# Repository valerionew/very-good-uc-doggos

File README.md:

# very-good-uc-doggos
A special graduation present for a special friend. Six microcontrollers in one devboard

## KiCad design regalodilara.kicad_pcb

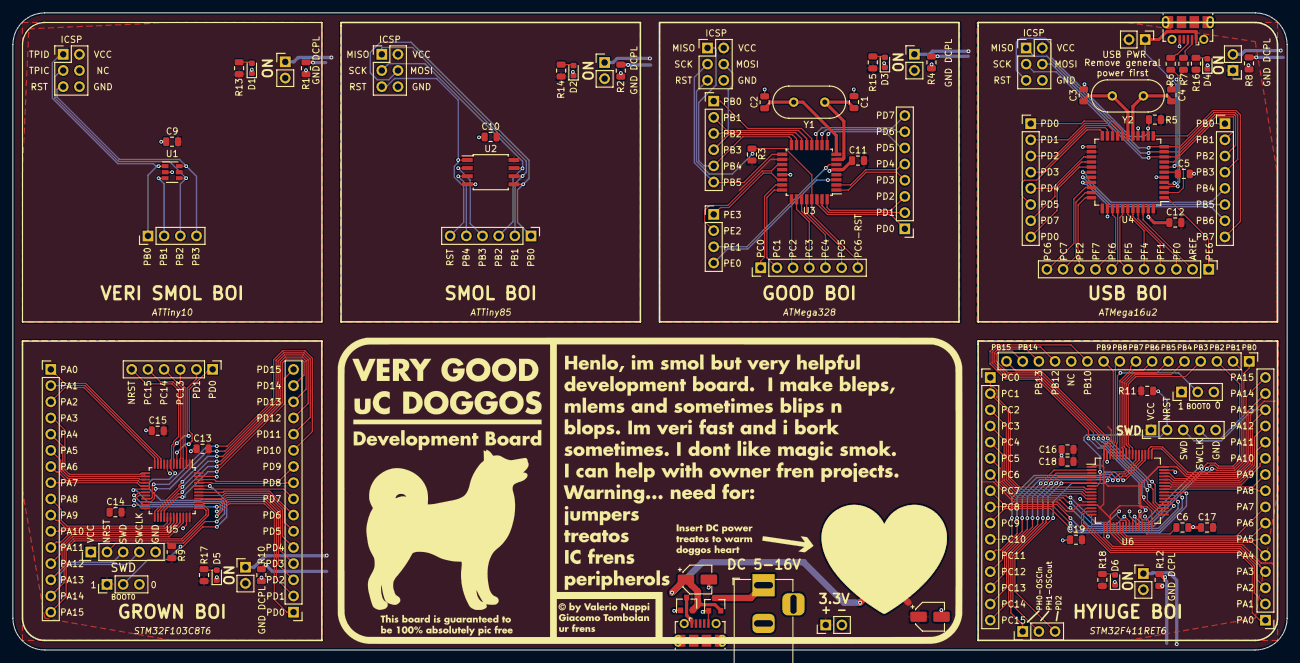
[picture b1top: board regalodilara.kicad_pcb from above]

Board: 2 copper layers, 200.0 x 100.0 mm, 89 parts (0 on the bottom side), 188 nets.

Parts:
C1, C2, C3, C4: C_Small; C_0805_2012Metric
C5: 1u; C_0805_2012Metric
C6: 2.2u; C_0805_2012Metric
C7, C8: 10u; CP_Elec_4x5.4
C9, C10, C11, C12, C13, C14, C15, C16, C17, C18, C19: 100n; C_0805_2012Metric
D1, D2, D3, D4, D5, D6: LED; LED_0603_1608Metric
J1, J4, J9, J13: ICSP; PinHeader_2x03_P2.54mm_Vertical
J2, J5, J7, J18, J24, J33: Conn_01x02; PinHeader_1x02_P2.54mm_Vertical
J3, J11: Conn_01x04; PinHeader_1x04_P2.54mm_Vertical
J6, J8: Conn_01x06; PinHeader_1x06_P2.54mm_Vertical
J10: Conn_01x07; PinHeader_1x07_P2.54mm_Vertical
J12, J14, J15: Conn_01x08; PinHeader_1x08_P2.54mm_Vertical
J16, J32: USB_B_Micro; USB_Micro-B_Molex-105017-0001
J17: Conn_01x11; PinHeader_1x11_P2.54mm_Vertical
J19, J26, J28: Conn_01x03; PinHeader_1x03_P2.54mm_Vertical
J20, J25: Conn_01x05; PinHeader_1x05_P2.54mm_Vertical
J21: Conn_01x05; PinHeader_1x06_P2.54mm_Vertical
J22, J23, J27, J29, J30: Conn_01x16; PinHeader_1x16_P2.54mm_Vertical
J31: Jack-DC; BarrelJack_Horizontal
JP1, JP2: Jumper_NO_Small; PinHeader_1x02_P2.54mm_Vertical
Q1, Q2: BSH203; SOT-23
R1, R2, R4, R10, R12: 0; R_0805_2012Metric
R3, R5, R9, R11: 10K; R_0805_2012Metric
R6, R7: 22R; R_0805_2012Metric
R8: R; R_0805_2012Metric
R13, R14, R15, R16, R17, R18: 220; R_0805_2012Metric
U1: ATtiny10-TS; SOT-23-6
U2: ATtiny85-20SU; SOIJ-8_5.3x5.3mm_P1.27mm
U3: ATmega328PB-AU; TQFP-32_7x7mm_P0.8mm
U4: ATmega32U4-AU; TQFP-44_10x10mm_P0.8mm
U5: STM32F103C8Tx; LQFP-48_7x7mm_P0.5mm
U6: STM32F411RETx; LQFP-64_10x10mm_P0.5mm
U7: LF33_TO252; TO-252-2
Y1: Crystal; Crystal_HC49-4H_Vertical
Y2: 20M; Crystal_HC49-4H_Vertical

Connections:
+VDC: C7.1, Q1.2, Q2.2, U7.1
/f103/NRST: J20.2, J21.6, R9.2, U5.7
/f103/SWCLK: J20.4, J23.15, U5.37
/f103/SWD: J20.3, J23.14, U5.34
/f103/UGND: C13.1, C14.1, C15.1, D5.1, J19.3, J20.5, R10.1, U5.8, U5.23, U5.35, U5.47
/f103/UVCC: C13.2, C14.2, C15.2, J18.2, J19.1, J20.1, R9.1, R17.1, U5.1, U5.9, U5.24, U5.36, U5.48
/f411/NRST: J25.2, R11.2, U6.7
/f411/SWCLK: J25.4, J27.15, U6.49
/f411/SWD: J25.3, J27.14, U6.46
/f411/UGND: C6.2, C16.1, C17.1, C18.1, C19.1, D6.1, J25.5, J26.3, R12.1, U6.12, U6.18, U6.31, U6.47, U6.63
/f411/UVCC: C16.2, C17.2, C18.2, C19.2, J24.2, J25.1, J26.1, R11.1, R18.1, U6.1, U6.13, U6.19, U6.32, U6.48, U6.64
/mega32u4/AREF: J17.2, U4.42
/mega32u4/MISO: J13.1, J14.4, U4.11
/mega32u4/MOSI: J13.4, J14.3, U4.10
/mega32u4/PC6: J17.11, U4.31
/mega32u4/PC7: J17.10, U4.32
/mega32u4/PE2: J17.9, U4.33
/mega32u4/RESET: J13.5, R5.2, U4.13
/mega32u4/SCK: J13.3, J14.2, U4.9
/mega32u4/UGND: C3.2, C4.1, C5.2, C12.1, D4.1, J13.6, J16.5, J16.6, R8.1, U4.5, U4.15, U4.23, U4.35, U4.43
/mega32u4/USBD+: R6.1, U4.4
/mega32u4/USBD-: R7.1, U4.3
/mega32u4/USBVCC: J16.1, JP2.1, U4.2, U4.7
/mega32u4/UVCC: C12.2, J13.2, JP1.1, JP2.2, R5.1, R16.1, U4.14, U4.24, U4.34, U4.44
/mega328/MISO: J8.5, J9.1, U3.16
/mega328/MOSI: J8.4, J9.4, U3.15
/mega328/RESET: J9.5, J10.7, R3.2, U3.29
/mega328/SCK: J8.6, J9.3, U3.17
/mega328/UGND: C1.1, C2.1, C11.1, D3.1, J9.6, R4.1, U3.5, U3.21
/mega328/UVCC: C11.2, J7.2, J9.2, R3.1, R15.1, U3.4, U3.18
/tiny10/RESET: J1.5, J3.4, U1.6
/tiny10/TPICLK: J1.3, J3.3, U1.4
/tiny10/TPIDATA: J1.1, J3.1, U1.1
/tiny10/UGND: C9.1, D1.1, J1.6, R1.1, U1.2
/tiny10/UVCC: C9.2, J1.2, J2.2, R13.1, U1.5
/tiny85/MISO: J4.1, J6.2, U2.6
/tiny85/MOSI: J4.4, J6.1, U2.5
/tiny85/RESET: J4.5, J6.6, U2.1
/tiny85/SCK: J4.3, J6.3, U2.7
/tiny85/UGND: C10.1, D2.1, J4.6, R2.1, U2.4
/tiny85/UVCC: C10.2, J4.2, J5.2, R14.1, U2.8
GND: C7.2, C8.2, J31.2, J32.5, J32.6, J33.2, Q1.1, Q2.1, R1.2, R2.2, R4.2, R8.2, R10.2, R12.2, U7.2
unnamed: C1.2, U3.7, Y1.1
unnamed: C2.2, U3.8, Y1.2
unnamed: C3.1, U4.17, Y2.1
unnamed: C4.2, U4.16, Y2.2
unnamed: C5.1, U4.6
unnamed: C6.1, U6.30
unnamed: D1.2, R13.2
unnamed: D2.2, R14.2
unnamed: D3.2, R15.2
unnamed: D4.2, R16.2
unnamed: D5.2, R17.2
unnamed: D6.2, R18.2
unnamed: J3.2, U1.3
unnamed: J6.4, U2.2
unnamed: J6.5, U2.3
unnamed: J8.1, U3.12
unnamed: J8.2, U3.13
unnamed: J8.3, U3.14
unnamed: J10.1, U3.23
unnamed: J10.2, U3.24
unnamed: J10.3, U3.25
unnamed: J10.4, U3.26
unnamed: J10.5, U3.27
unnamed: J10.6, U3.28
unnamed: J11.1, U3.22
unnamed: J11.2, U3.19
unnamed: J11.3, U3.6
unnamed: J11.4, U3.3
unnamed: J12.1, U3.30
unnamed: J12.2, U3.31
unnamed: J12.3, U3.32
unnamed: J12.4, U3.1
unnamed: J12.5, U3.2
unnamed: J12.6, U3.9
unnamed: J12.7, U3.10
unnamed: J12.8, U3.11
unnamed: J14.1, U4.8
unnamed: J14.5, U4.28
unnamed: J14.6, U4.29
unnamed: J14.7, U4.30
unnamed: J14.8, U4.12
unnamed: J15.1, U4.18
unnamed: J15.2, U4.19
unnamed: J15.3, U4.20
unnamed: J15.4, U4.21
unnamed: J15.5, U4.25
unnamed: J15.6, U4.22
unnamed: J15.7, U4.26
unnamed: J15.8, U4.27
unnamed: J16.2, R7.2
unnamed: J16.3, R6.2
unnamed: J17.1, U4.1
unnamed: J17.3, U4.41
unnamed: J17.4, U4.40
unnamed: J17.5, U4.39
unnamed: J17.6, U4.38
unnamed: J17.7, U4.37
unnamed: J17.8, U4.36
unnamed: J19.2, U5.44
unnamed: J21.1, U5.5
unnamed: J21.2, U5.6
unnamed: J21.3, U5.2
unnamed: J21.4, U5.3
unnamed: J21.5, U5.4
unnamed: J22.1, U5.18
unnamed: J22.2, U5.19
unnamed: J22.3, U5.20
unnamed: J22.4, U5.39
unnamed: J22.5, U5.40
unnamed: J22.6, U5.41
unnamed: J22.7, U5.42
unnamed: J22.8, U5.43
unnamed: J22.9, U5.45
unnamed: J22.10, U5.46
unnamed: J22.11, U5.21
unnamed: J22.12, U5.22
unnamed: J22.13, U5.25
unnamed: J22.14, U5.26
unnamed: J22.15, U5.27
unnamed: J22.16, U5.28
unnamed: J23.1, U5.10
unnamed: J23.2, U5.11
unnamed: J23.3, U5.12
unnamed: J23.4, U5.13
unnamed: J23.5, U5.14
unnamed: J23.6, U5.15
unnamed: J23.7, U5.16
unnamed: J23.8, U5.17
unnamed: J23.9, U5.29
unnamed: J23.10, U5.30
unnamed: J23.11, U5.31
unnamed: J23.12, U5.32
unnamed: J23.13, U5.33
unnamed: J23.16, U5.38
unnamed: J26.2, U6.60
unnamed: J27.1, U6.14
unnamed: J27.2, U6.15
unnamed: J27.3, U6.16
unnamed: J27.4, U6.17
unnamed: J27.5, U6.20
unnamed: J27.6, U6.21
unnamed: J27.7, U6.22
unnamed: J27.8, U6.23
unnamed: J27.9, U6.41
unnamed: J27.10, U6.42
unnamed: J27.11, U6.43
unnamed: J27.12, U6.44
unnamed: J27.13, U6.45
unnamed: J27.16, U6.50
unnamed: J28.1, U6.5
unnamed: J28.2, U6.6
unnamed: J28.3, U6.54
unnamed: J29.1, U6.8
unnamed: J29.2, U6.9
unnamed: J29.3, U6.10
unnamed: J29.4, U6.11
unnamed: J29.5, U6.24
unnamed: J29.6, U6.25
unnamed: J29.7, U6.37
unnamed: J29.8, U6.38
unnamed: J29.9, U6.39
unnamed: J29.10, U6.40
unnamed: J29.11, U6.51
unnamed: J29.12, U6.52
unnamed: J29.13, U6.53
unnamed: J29.14, U6.2
unnamed: J29.15, U6.3
unnamed: J29.16, U6.4
unnamed: J30.1, U6.26
unnamed: J30.2, U6.27
unnamed: J30.3, U6.28
unnamed: J30.4, U6.55
unnamed: J30.5, U6.56
unnamed: J30.6, U6.57
unnamed: J30.7, U6.58
unnamed: J30.8, U6.59
unnamed: J30.9, U6.61
unnamed: J30.10, U6.62
unnamed: J30.11, U6.29
unnamed: J30.13, U6.33
unnamed: J30.14, U6.34
unnamed: J30.15, U6.35
unnamed: J30.16, U6.36
unnamed: J31.1, Q2.3
unnamed: J32.1, Q1.3
VCC: C8.1, J2.1, J5.1, J7.1, J18.1, J24.1, J33.1, JP1.2, U7.3

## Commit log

2019-10-03 added private folder to gitignore
2019-10-03 first commit of v1
2019-10-03 added images to readme
2019-10-03 added license files
2019-10-03 added pdf schematic

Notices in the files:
regalodilara.kicad_pcb:
Artworks: Giacomo Tombolan (CC-BY-NC-4.0)
https://creativecommons.org/licenses/by-nc/4.0
Hardware design: Valerio Nappi (CERN OHL 1.2)
